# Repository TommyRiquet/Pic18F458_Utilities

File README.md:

# Projet d'Electronique

Ce repo est utilisé dans le cadre scolaire afin d'heberger les différents fichiers utilisé lors de l'utilisation d'un PIC18F458  
<br>

## Comment l'utiliser ?

Tout d'abord, récuperez les différents fichiers avec ``git clone https://github.com/TommyRiquet/Pic18F458_Utilities``  

Le fichier [main.hex](https://github.com/TommyRiquet/Pic18F458_Utilities/blob/main/main.hex) est à ajouter à votre micro-controlleur PIC, il s'agit des instructions et le comportement de ce dernier  

Le fichier [InterfacePython.py](https://github.com/TommyRiquet/Pic18F458_Utilities/blob/main/InterfacePython.py) est utilisé comme interface entre le micro-controlleur et l'ordinateur

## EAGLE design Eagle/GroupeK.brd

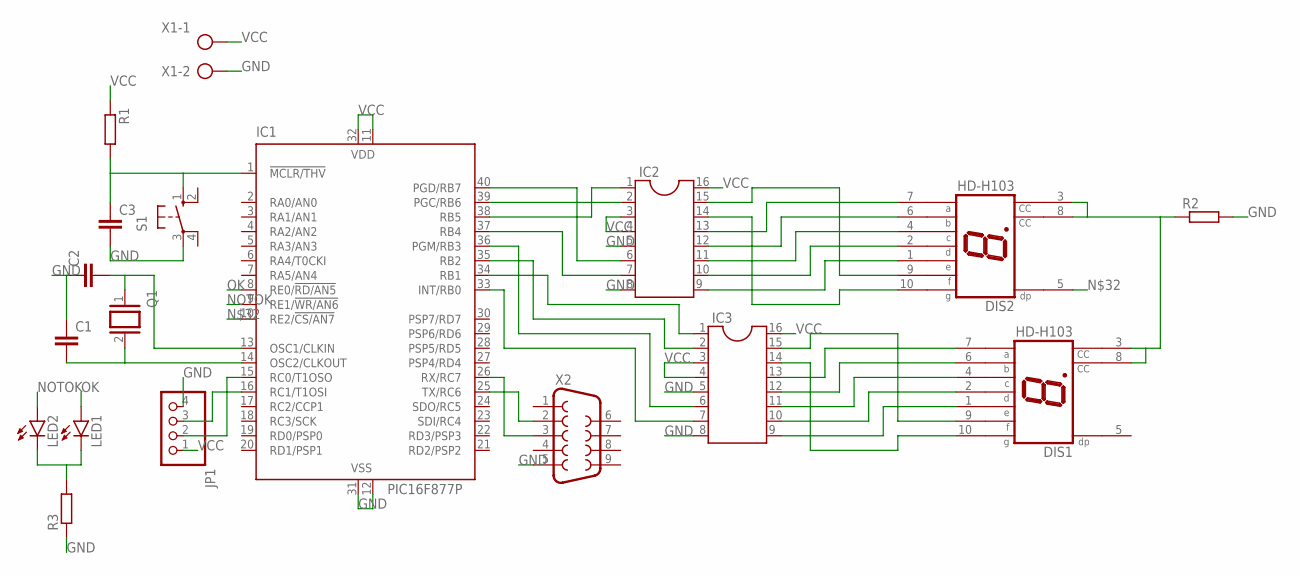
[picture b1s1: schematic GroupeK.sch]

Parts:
C1, C2, C3: C-EU025-025X050; C025-025X050
DIS1, DIS2: HD-H103; HDSP-M
IC1: PIC16F877P; DIL40
IC2, IC3: DIL16
JP1: PINHD-1X4; 1X04
LED1, LED2: LED5MM
Q1: XTAL/S; QS
R1, R2, R3: R-EU_0207/10; 0207/10
S1: 10-XX; B3F-10XX
X1: AK300/2
X2: F09H

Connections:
GND: C1.1, C2.1, C3.2, IC1.12 (VSS), IC1.31 (VSS), IC2.5, IC2.8, IC3.5, IC3.8, JP1.4, R2.2, R3.1, S1.3, X1.2, X2.5
unnamed: DIS1.3 (CC), DIS1.8 (CC), DIS2.3 (CC), DIS2.8 (CC), R2.1
unnamed: IC1.15 (RC0/T1OSO), JP1.2
unnamed: C3.1, IC1.1 (!MCLR/THV), R1.2, S1.1 (S)
unnamed: C1.2, IC1.14 (OSC2/CLKOUT), Q1.2
unnamed: IC1.26 (RX/RC7), X2.3
unnamed: C2.2, IC1.13 (OSC1/CLKIN), Q1.1
unnamed: DIS2.7 (A), IC2.13
unnamed: IC1.39 (PGC/RB6), IC2.2
unnamed: IC1.40 (PGD/RB7), IC2.6
unnamed: DIS2.6 (B), IC2.12
unnamed: IC1.37 (RB4), IC2.7
unnamed: IC1.38 (RB5), IC2.1
unnamed: DIS2.4 (C), IC2.11
unnamed: DIS2.2 (D), IC2.10
unnamed: DIS2.1 (E), IC2.9
unnamed: DIS2.9 (F), IC2.15
unnamed: DIS2.10 (G), IC2.14
unnamed: LED1.K (C), LED2.K (C), R3.2
unnamed: DIS1.7 (A), IC3.13
unnamed: DIS1.6 (B), IC3.12
unnamed: DIS1.4 (C), IC3.11
unnamed: DIS1.2 (D), IC3.10
unnamed: DIS1.1 (E), IC3.9
unnamed: DIS1.9 (F), IC3.15
unnamed: DIS1.10 (G), IC3.14
unnamed: IC1.25 (TX/RC6), X2.2
unnamed: IC1.34 (RB1), IC3.1
unnamed: IC1.35 (RB2), IC3.2
unnamed: IC1.36 (PGM/RB3), IC3.6
unnamed: IC1.33 (INT/RB0), IC3.7
unnamed: DIS2.5 (DP), IC1.10 (RE2/!CS/AN7)
unnamed: IC1.16 (RC1/T1OSI), JP1.3
NOTOK: IC1.9 (RE1/!WR/AN6), LED2.A
OK: IC1.8 (RE0/!RD/AN5), LED1.A
VCC: IC1.11 (VDD), IC1.32 (VDD), IC2.3, IC2.4, IC2.16, IC3.3, IC3.4, IC3.16, JP1.1, R1.1, X1.1

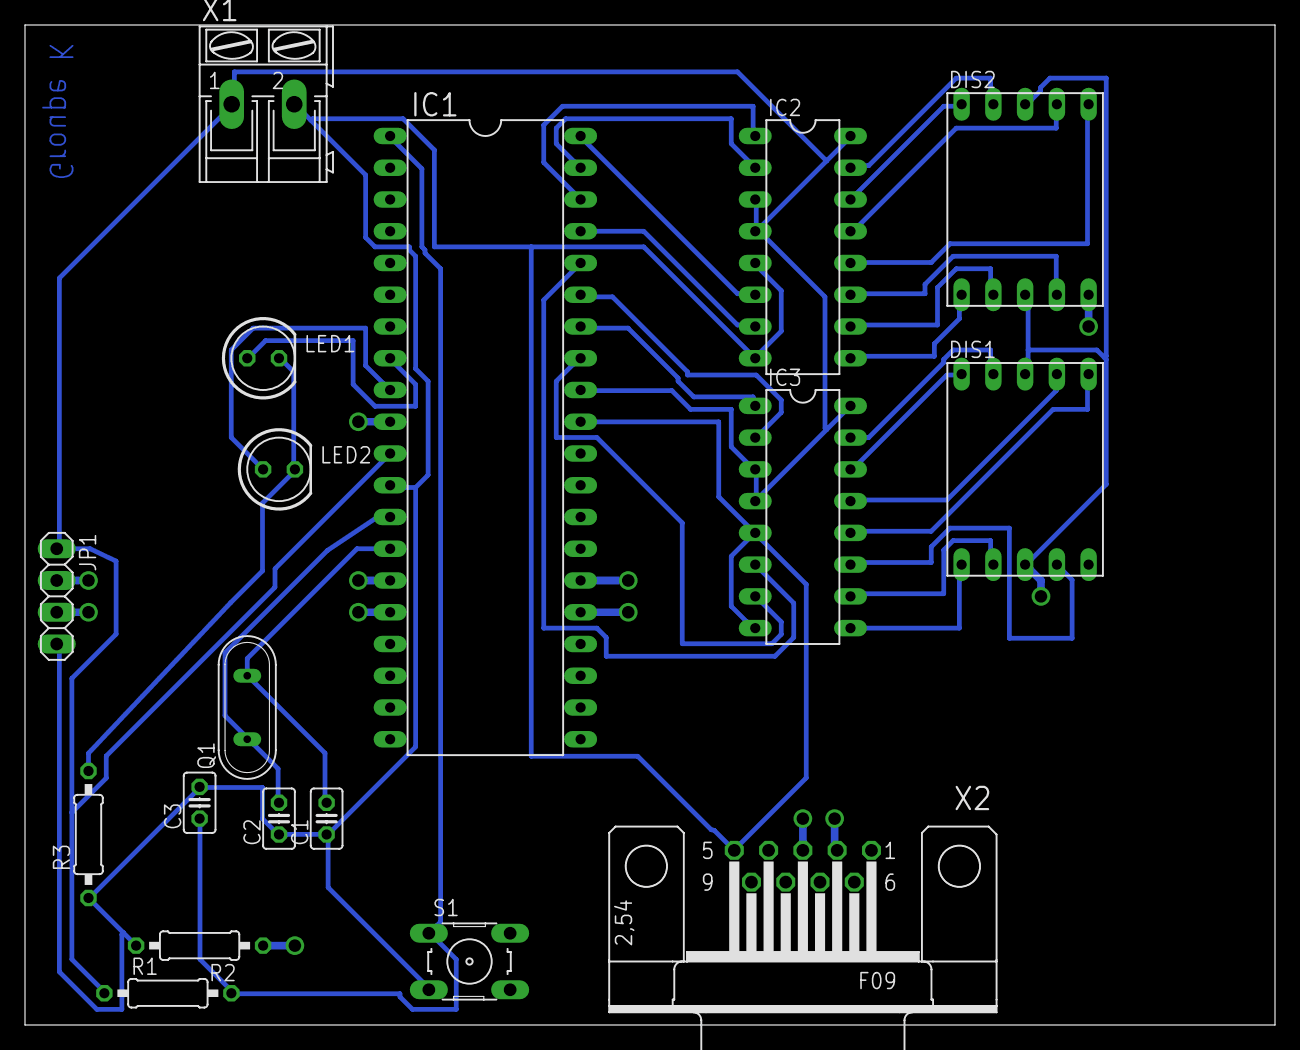
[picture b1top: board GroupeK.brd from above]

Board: 2 copper layers, 100.0 x 80.0 mm, 18 parts (0 on the bottom side), 36 nets.

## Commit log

2022-05-04 Rename main.hex to Code C/main.hex
2022-05-04 Rename main.ccspjt to Code C/main.ccspjt
2022-05-04 Rename main.c to Code C/main.c
2022-05-04 Rename main.h to Code C/main.h
2022-05-04 Rename script.hex to Code C/script.hex
2022-05-04 Rename InterfacePython.py to Code Python/InterfacePython.py
2022-05-04 Rename GroupeK.brd to Eagle/GroupeK.brd
2022-05-04 Rename CGroupeK.sch to Eagle/GroupeK.sch
2022-05-11 Interface Python
